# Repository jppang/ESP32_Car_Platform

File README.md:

# ESP32_Car_Platform
To design a four wheels Mecanum car platform controlled by Dabble App in Arduino and MicroPython.

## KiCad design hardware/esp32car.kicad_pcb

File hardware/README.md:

Hardware design of this ESP32 car platform is by using KiCad 6.

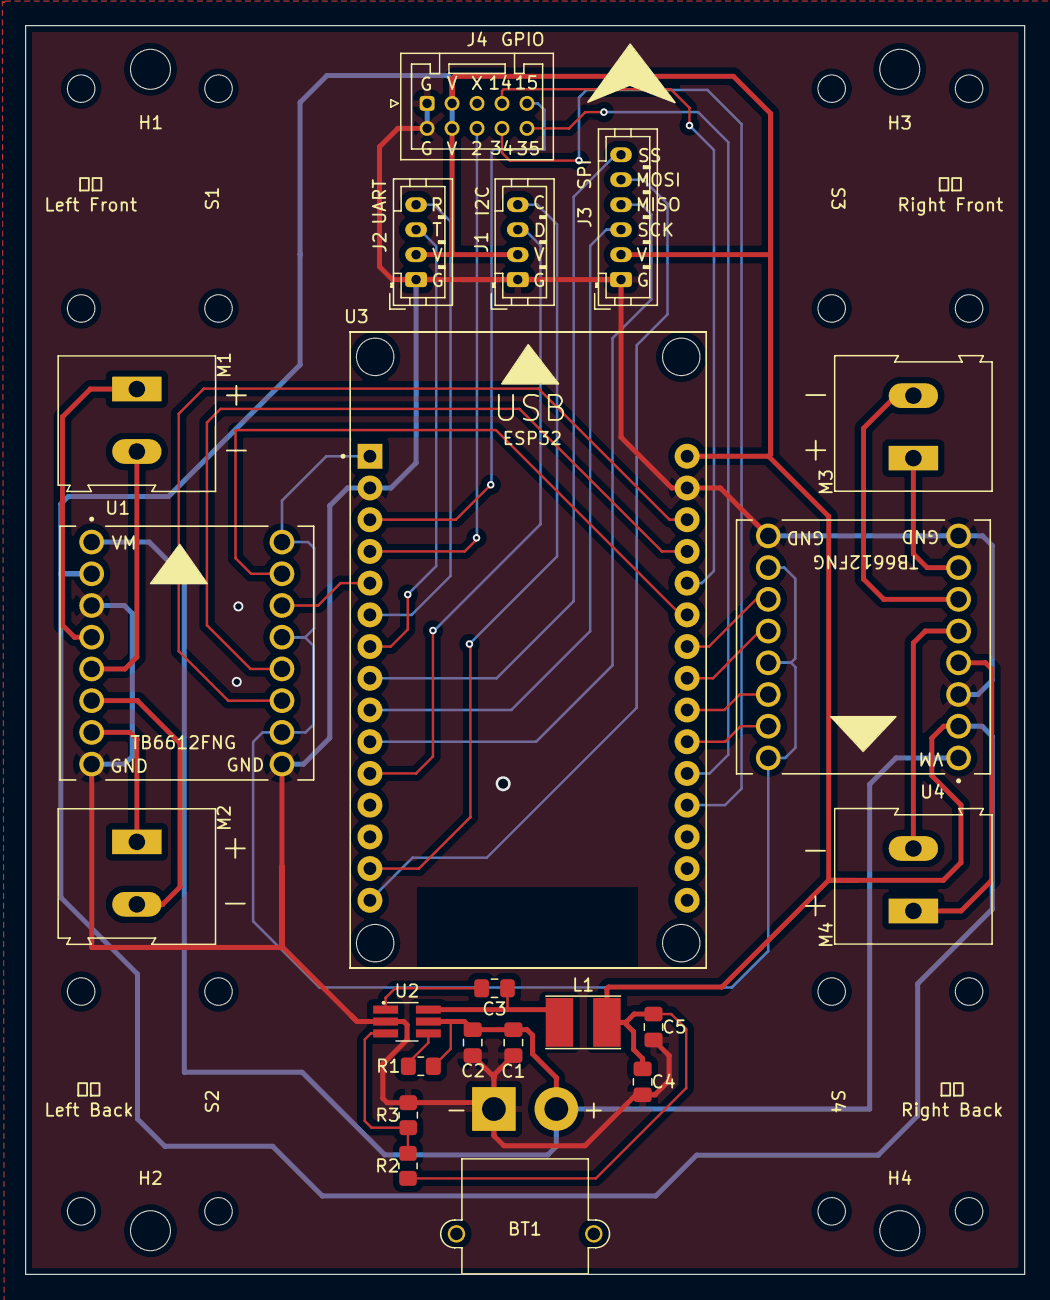
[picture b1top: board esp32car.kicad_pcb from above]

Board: 2 copper layers, 80.0 x 100.0 mm, 30 parts (0 on the bottom side), 37 nets.

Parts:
BT1: 2or3S; AMASS_XT30PW-M_1x02_P2.50mm_Horizontal
C1, C5: 22uF; C_0805_2012Metric_Pad1.18x1.45mm_HandSolder
C2, C3, C4: 0.1uF; C_0805_2012Metric_Pad1.18x1.45mm_HandSolder
H1, H2, H3, H4: MountingHole; MountingHole_3.2mm_M3
J1: I2C; JST_PH_B4B-PH-K_1x04_P2.00mm_Vertical
J2: UART; JST_PH_B4B-PH-K_1x04_P2.00mm_Vertical
J3: SPI; JST_PH_B6B-PH-K_1x06_P2.00mm_Vertical
J4: GPIO; JST_PUD_B10B-PUDSS_2x05_P2.00mm_Vertical
L1: 3.3uH; L_Taiyo-Yuden_NR-40xx_HandSoldering
M1: LeftFront; TerminalBlock_Altech_AK300-2_P5.00mm
M2: LeftBack; TerminalBlock_Altech_AK300-2_P5.00mm
M3: RightFront; TerminalBlock_Altech_AK300-2_P5.00mm
M4: RightBack; TerminalBlock_Altech_AK300-2_P5.00mm
R1: 200K; R_0805_2012Metric_Pad1.20x1.40mm_HandSolder
R2: 24.6K; R_0805_2012Metric_Pad1.20x1.40mm_HandSolder
R3: 4.7K; R_0805_2012Metric_Pad1.20x1.40mm_HandSolder
S1, S2, S3, S4: Mounting_Jack_N20_Motor; MountingHole_N20_Motor_2.2mm_M2
U1: TB6612FNG-Left; MODULE_ROB-14450
U2: PW2312; TSOT-23-6_HandSoldering
U3: ESP32-DEVKIT-V1; MODULE_ESP32_DEVKIT_V1
U4: TB6612FNG-Right; MODULE_ROB-14450

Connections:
+3V3: U1.10 (PWMB), U1.13 (STBY), U1.16 (PWMA), U3.1 (3V3), U4.10 (PWMB), U4.13 (STBY), U4.16 (PWMA)
+5V: C4.1, C5.1, J1.2, J2.2, J3.2, J4.3, J4.4, L1.2, R2.1, U1.2 (VCC), U3.30 (VIN), U4.2 (VCC)
+BATT: BT1.2 (+), C1.1, C2.1, R1.1, U1.1 (VM), U2.5 (VIN), U4.1 (VM)
/2: J4.6, U3.4 (D2)
/14: J4.7, U3.26 (D14)
/15: J4.9, U3.3 (D15)
/34: J4.8, U3.19 (D34)
/35: J4.10, U3.20 (D35)
/LBBWD: U1.11 (BI2), U3.28 (D13)
/LBFWD: U1.12 (BI1), U3.27 (D12)
/LFBWD: U1.15 (AI2), U3.25 (D27)
/LFFWD: U1.14 (AI1), U3.5 (D4)
/LeftBackBWD: M2.2 (-), U1.6 (B02)
/LeftBackFWD: M2.1 (+), U1.7 (B01)
/LeftFrontBWD: M1.2 (-), U1.5 (A02)
/LeftFrontFWD: M1.1 (+), U1.4 (A01)
/MISO: J3.4, U3.10 (D19)
/MOSI: J3.5, U3.15 (D23)
/RBBWD: U3.21 (D32), U4.15 (AI2)
/RBFWD: U3.22 (D33), U4.14 (AI1)
/RFBWD: U3.24 (D26), U4.11 (BI2)
/RFFWD: U3.23 (D25), U4.12 (BI1)
/RX: J2.4, U3.6 (RX2)
/RightBackBWD: M4.2 (-), U4.5 (A02)
/RightBackFWD: M4.1 (+), U4.4 (A01)
/RightFrontBWD: M3.2 (-), U4.6 (B02)
/RightFrontFWD: M3.1 (+), U4.7 (B01)
/SCK: J3.3, U3.9 (D18)
/SCL: J1.4, U3.14 (D22)
/SDA: J1.3, U3.11 (D21)
/SS: J3.6, U3.8 (D5)
/TX: J2.3, U3.7 (TX2)
GND: BT1.1 (-), C1.2, C2.2, C4.2, C5.2, J1.1, J2.1, J3.1, J4.1, J4.2, R3.2, U1.3 (GND), U1.8 (GND), U1.9 (GND), U2.2 (GND), U3.2 (GND), U3.29 (GND), U4.3 (GND), U4.8 (GND), U4.9 (GND)
unnamed: C3.1, U2.1 (BS)
unnamed: C3.2, L1.1, U2.6 (SW)
unnamed: R1.2, U2.4 (EN)
unnamed: R2.2, R3.1, U2.3 (FB)

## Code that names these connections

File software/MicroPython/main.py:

from machine import Pin
from ble import BLE

RightFrontFWD = 26
RightFrontBWD = 25
RightBackFWD = 32
RightBackBWD = 33

LeftFrontFWD = 4
LeftFrontBWD = 27
LeftBackFWD = 12
LeftBackBWD = 13

#Dabble App message is consisted of 8 bytes, and those commands associated with GamePad are in the combination of
#6th and 7th bytes of this message.
UP = b'\x00\x01'
DOWN = b'\x00\x02'
LEFT = b'\x00\x04'
RIGHT = b'\x00\x08'
TRIANGLE = b'\x04\x00'
CROSS = b'\x10\x00'
SQUARE = b' \x00'
CIRCLE = b'\x08\x00'
SELECT = b'\x02\x00'
START = b'\x01\x00'

mode = bytearray()

rfFWD = Pin(RightFrontFWD, Pin.OUT)
rfBWD = Pin(RightFrontBWD, Pin.OUT)
rbFWD = Pin(RightBackFWD, Pin.OUT)
rbBWD = Pin(RightBackBWD, Pin.OUT)
lfFWD = Pin(LeftFrontFWD, Pin.OUT)
lfBWD = Pin(LeftFrontBWD, Pin.OUT)
lbFWD = Pin(LeftBackFWD, Pin.OUT)
lbBWD = Pin(LeftBackBWD, Pin.OUT)

def moveForward():
    rfFWD.on()
    rfBWD.off()
    rbFWD.on()
    rbBWD.off()

    lfFWD.on()
    lfBWD.off()
    lbFWD.on()
    lbBWD.off()

def moveBackward():
    rfFWD.off()
    rfBWD.on()
    rbFWD.off()
    rbBWD.on()

    lfFWD.off()
    lfBWD.on()
    lbFWD.off()
    lbBWD.on()

def rotateRight():
    rfFWD.off()
    rfBWD.on()
    rbFWD.off()
    rbBWD.on()

    lfFWD.on()
    lfBWD.off()
    lbFWD.on()
    lbBWD.off()

def rotateLeft():
    rfFWD.on()
    rfBWD.off()
    rbFWD.on()
    rbBWD.off()

    lfFWD.off()
    lfBWD.on()
    lbFWD.off()
    lbBWD.on()

def moveSidewaysRight():
    rfFWD.off()
    rfBWD.on()
    rbFWD.on()
    rbBWD.off()

    lfFWD.on()
    lfBWD.off()
    lbFWD.off()
    lbBWD.on()

def moveSidewaysLeft():
    rfFWD.on()
    rfBWD.off()
    rbFWD.off()
    rbBWD.on()

    lfFWD.off()
    lfBWD.on()
    lbFWD.on()
    lbBWD.off()

def moveRightForward():
    rfFWD.off()
    rfBWD.off()
    rbFWD.on()
    rbBWD.off()

    lfFWD.on()
    lfBWD.off()
    lbFWD.off()
    lbBWD.off()

def moveLeftForward():
    rfFWD.on()
    rfBWD.off()
    rbFWD.off()
    rbBWD.off()

    lfFWD.off()
    lfBWD.off()
    lbFWD.on()
    lbBWD.off()

def stopMoving():
    rfFWD.off()
    rfBWD.off()
    rbFWD.off()
    rbBWD.off()

    lfFWD.off()
    lfBWD.off()
    lbFWD.off()
    lbBWD.off()

ble = BLE()

while(True):
    if ble.flag == True:
        mode = ble.message[5:7]
        print(mode)
        ble.flag = False

        if mode == UP:
            print("UP is pressed.")
            moveForward()
        elif mode == DOWN:
            print("DOWN is pressed.")
            moveBackward()
        elif mode == LEFT:
            print("LEFT is pressed.")
            rotateLeft()
        elif mode == RIGHT:
            print("RIGHT is pressed.")
            rotateRight()
        elif mode == TRIANGLE:
            print("TRIANGLE is pressed.")
            moveLeftForward()
        elif mode == CROSS:
            print("CROSS is pressed.")
            moveRightForward()
        elif mode == SQUARE:
            print("SQUARE is pressed.")
            moveSidewaysLeft()
        elif mode == CIRCLE:
            print("CIRCLE is pressed.")
            moveSidewaysRight()
        elif mode == SELECT:
            print("SELECT is pressed.")
        elif mode == START:
            print("START is pressed.")
        else:
            stopMoving()
